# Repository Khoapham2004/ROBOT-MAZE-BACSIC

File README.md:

# ROBOT-MAZE-BACSIC
design in kicad : 
Arduino nano, HC-SR04, N20, Driver TB6612FNG, MPU, LM2596, Botton

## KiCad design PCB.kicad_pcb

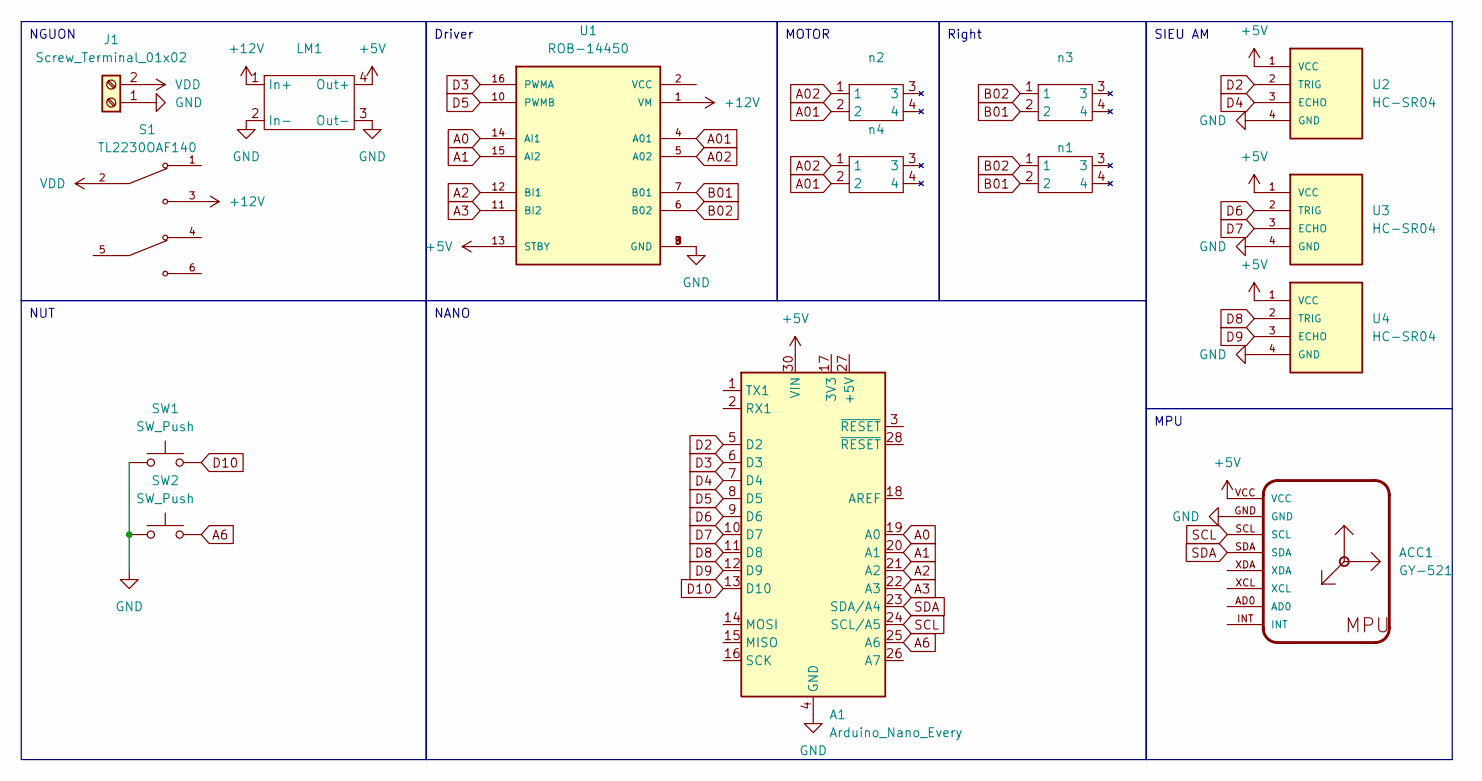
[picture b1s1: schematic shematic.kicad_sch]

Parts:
A1: Arduino_Nano_Every; Arduino_Nano
ACC1: GY-521
J1: Screw_Terminal_01x02; TerminalBlock_Phoenix_MKDS-1,5-2_1x02_P5.00mm_Horizontal
LM1: Lm2596
S1: TL2230OAF140; SW_6 pins 8.5×8.5MM; PARTREV E
SW1, SW2: SW_Push; SW_PUSH_6mm_H9.5mm
U1: ROB-14450; MODULE_ROB-14450; PARTREV 11-13-17
U2, U3, U4: HC-SR04; XCVR_HC-SR04
n1, n2, n3, n4: n20

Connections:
+5V: A1.30 (VIN), ACC1.VCC, LM1.4 (Out+), U1.13 (STBY), U2.1 (VCC), U3.1 (VCC), U4.1 (VCC)
+12V: LM1.1 (In+), S1.3, U1.1 (VM)
A0: A1.19 (A0), U1.14 (AI1)
A1: A1.20 (A1), U1.15 (AI2)
A01: U1.4 (A01), n2.2, n4.2
A2: A1.21 (A2), U1.12 (BI1)
A02: U1.5 (A02), n2.1, n4.1
A3: A1.22 (A3), U1.11 (BI2)
A6: A1.25 (A6), SW2.2
B01: U1.7 (B01), n1.2, n3.2
B02: U1.6 (B02), n1.1, n3.1
D2: A1.5 (D2), U2.2 (TRIG)
D3: A1.6 (D3), U1.16 (PWMA)
D4: A1.7 (D4), U2.3 (ECHO)
D5: A1.8 (D5), U1.10 (PWMB)
D6: A1.9 (D6), U3.2 (TRIG)
D7: A1.10 (D7), U3.3 (ECHO)
D8: A1.11 (D8), U4.2 (TRIG)
D9: A1.12 (D9), U4.3 (ECHO)
D10: A1.13 (D10), SW1.2
GND: A1.4 (GND), A1.29 (GND), ACC1.GND, J1.1, LM1.2 (In-), LM1.3 (Out-), SW1.1, SW2.1, U1.3 (GND), U1.8 (GND), U1.9 (GND), U2.4 (GND), U3.4 (GND), U4.4 (GND)
SCL: A1.24 (SCL/A5), ACC1.SCL
SDA: A1.23 (SDA/A4), ACC1.SDA
VDD: J1.2, S1.2

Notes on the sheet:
NGUON
NUT
SIEU AM
MPU
Right
NANO
MOTOR
Driver

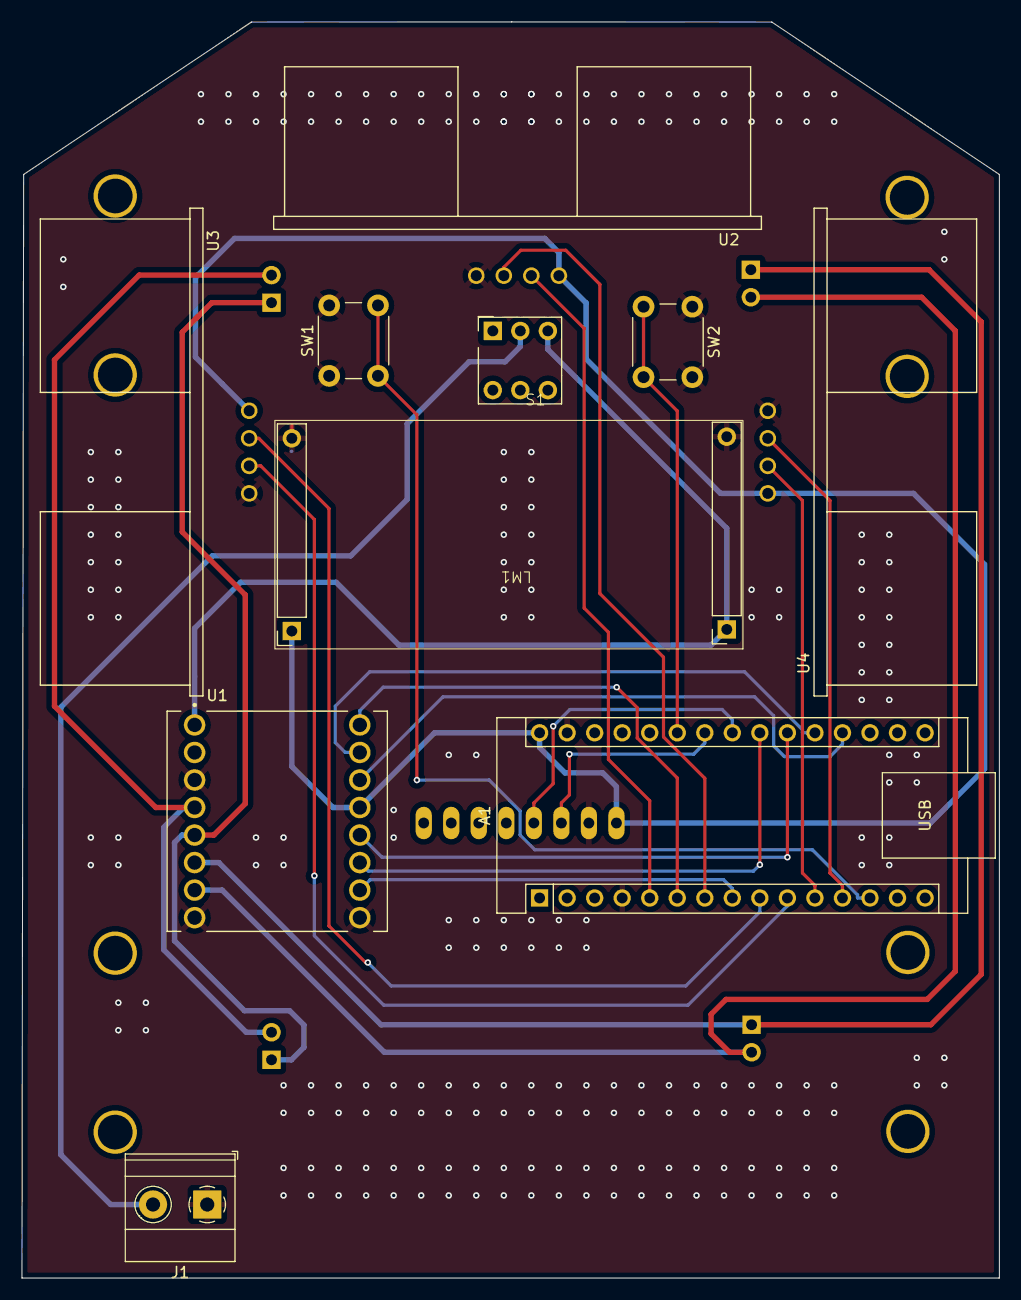
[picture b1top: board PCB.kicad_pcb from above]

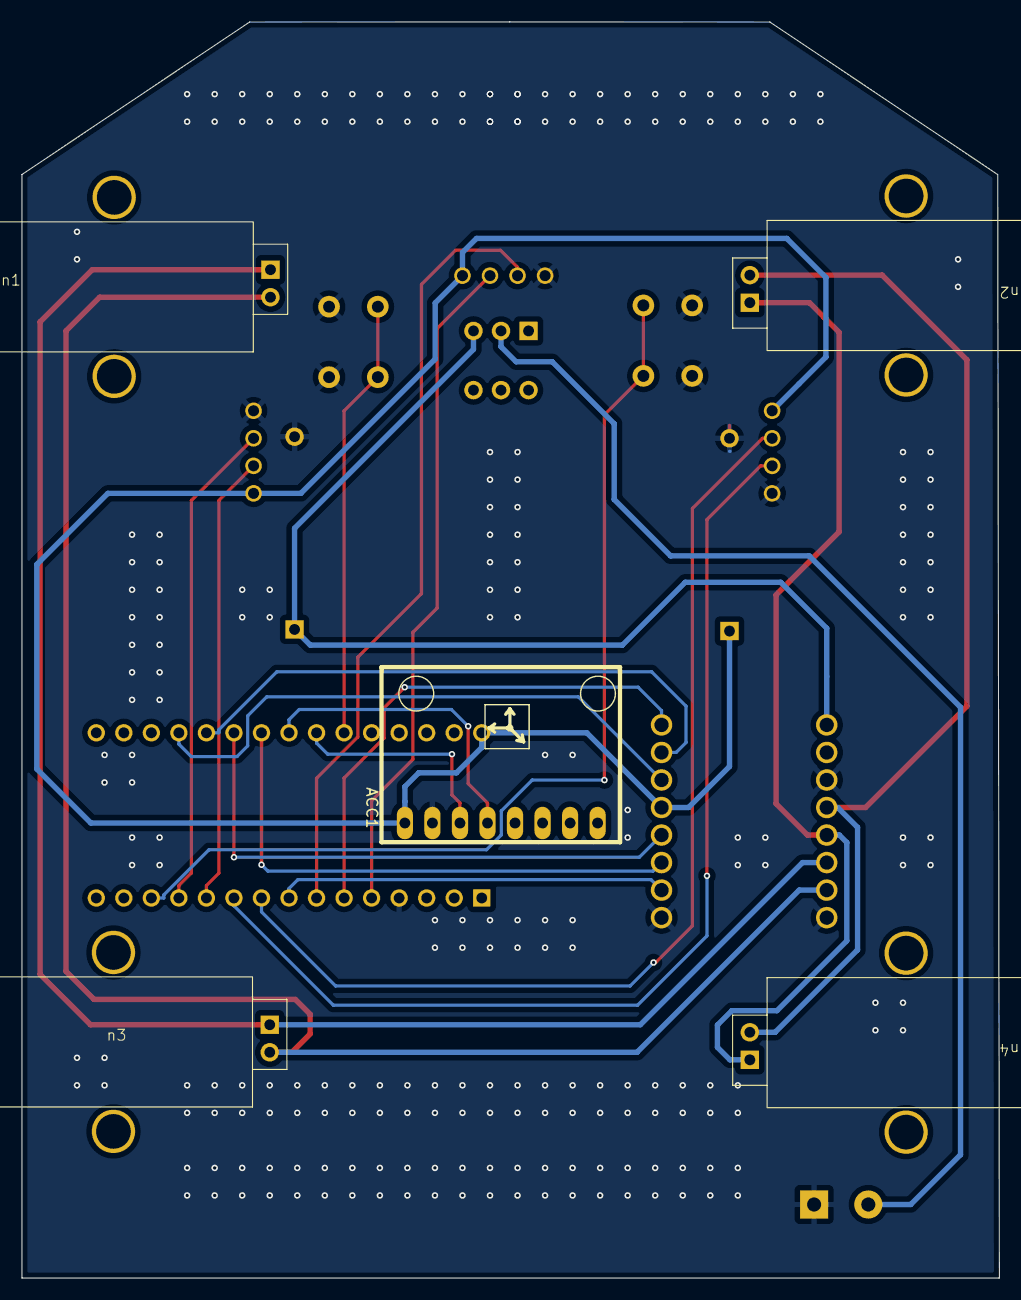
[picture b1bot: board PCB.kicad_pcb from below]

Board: 2 copper layers, 90.2 x 115.9 mm, 15 parts (5 on the bottom side), 24 nets.

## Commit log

2025-04-26 Rename CO_MPU_quay90.ino to main.ino
2025-05-03 Create Maze
2025-05-03 Rename Maze to Maze.cpp
